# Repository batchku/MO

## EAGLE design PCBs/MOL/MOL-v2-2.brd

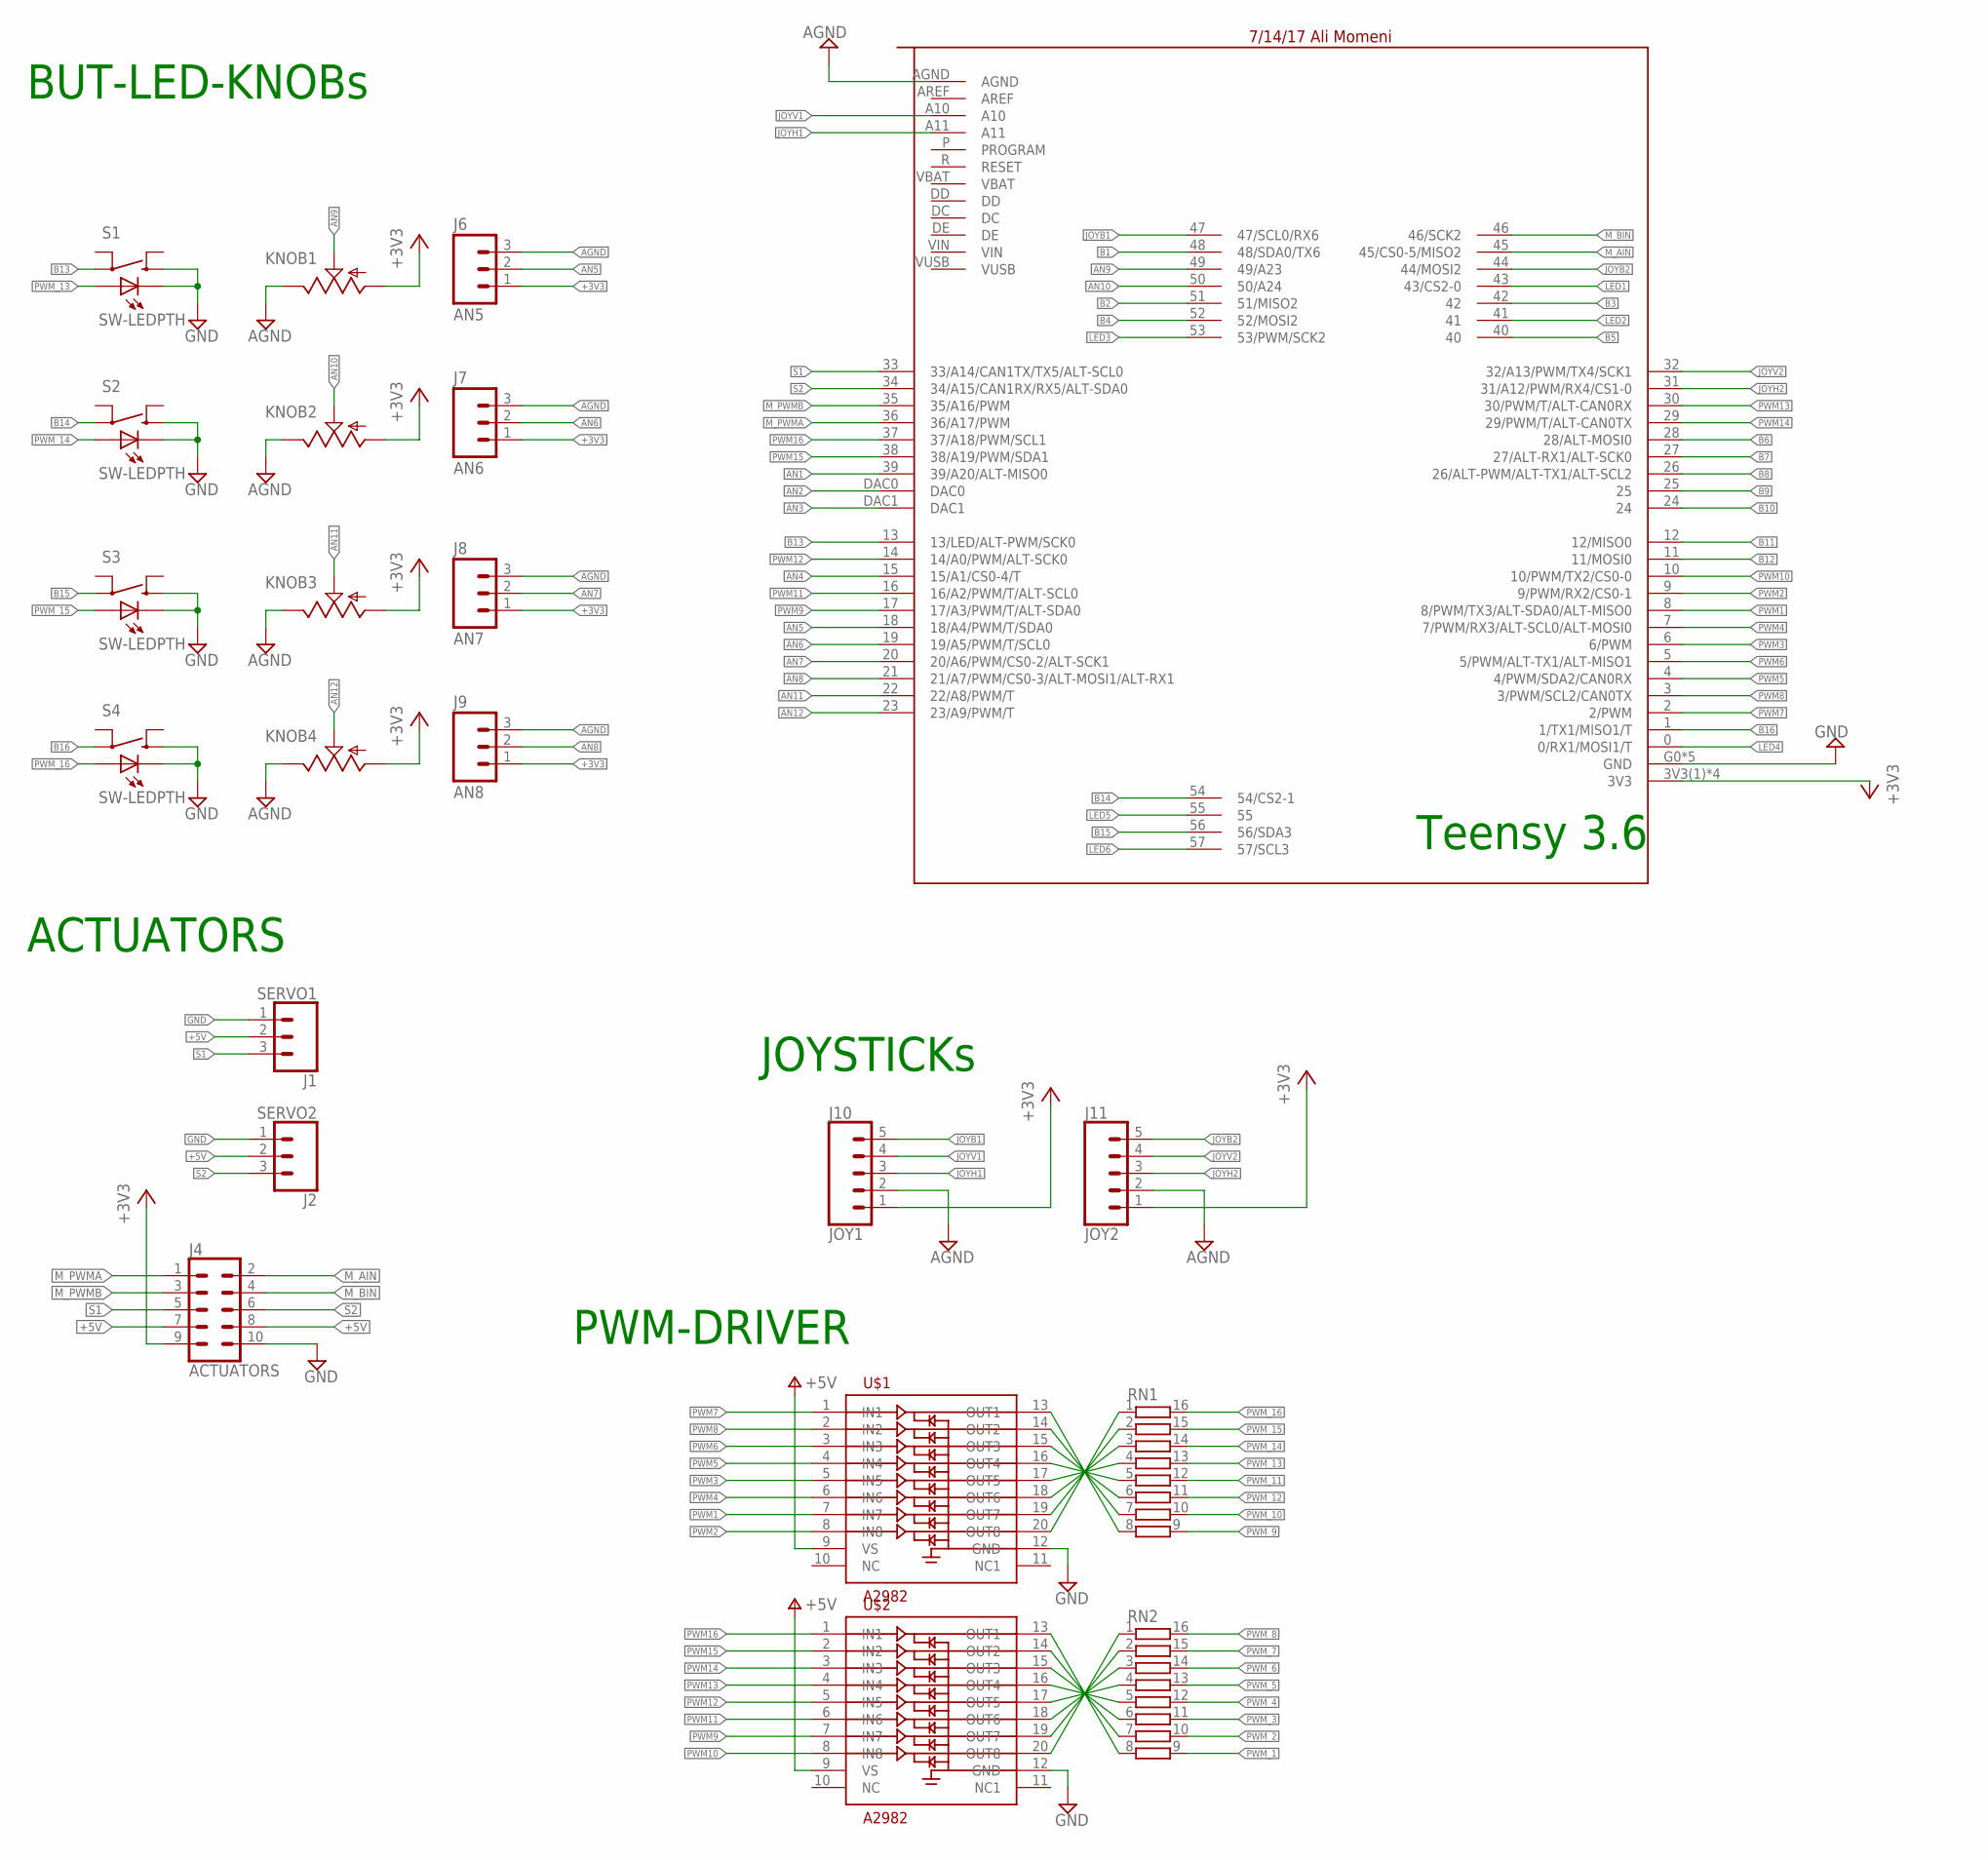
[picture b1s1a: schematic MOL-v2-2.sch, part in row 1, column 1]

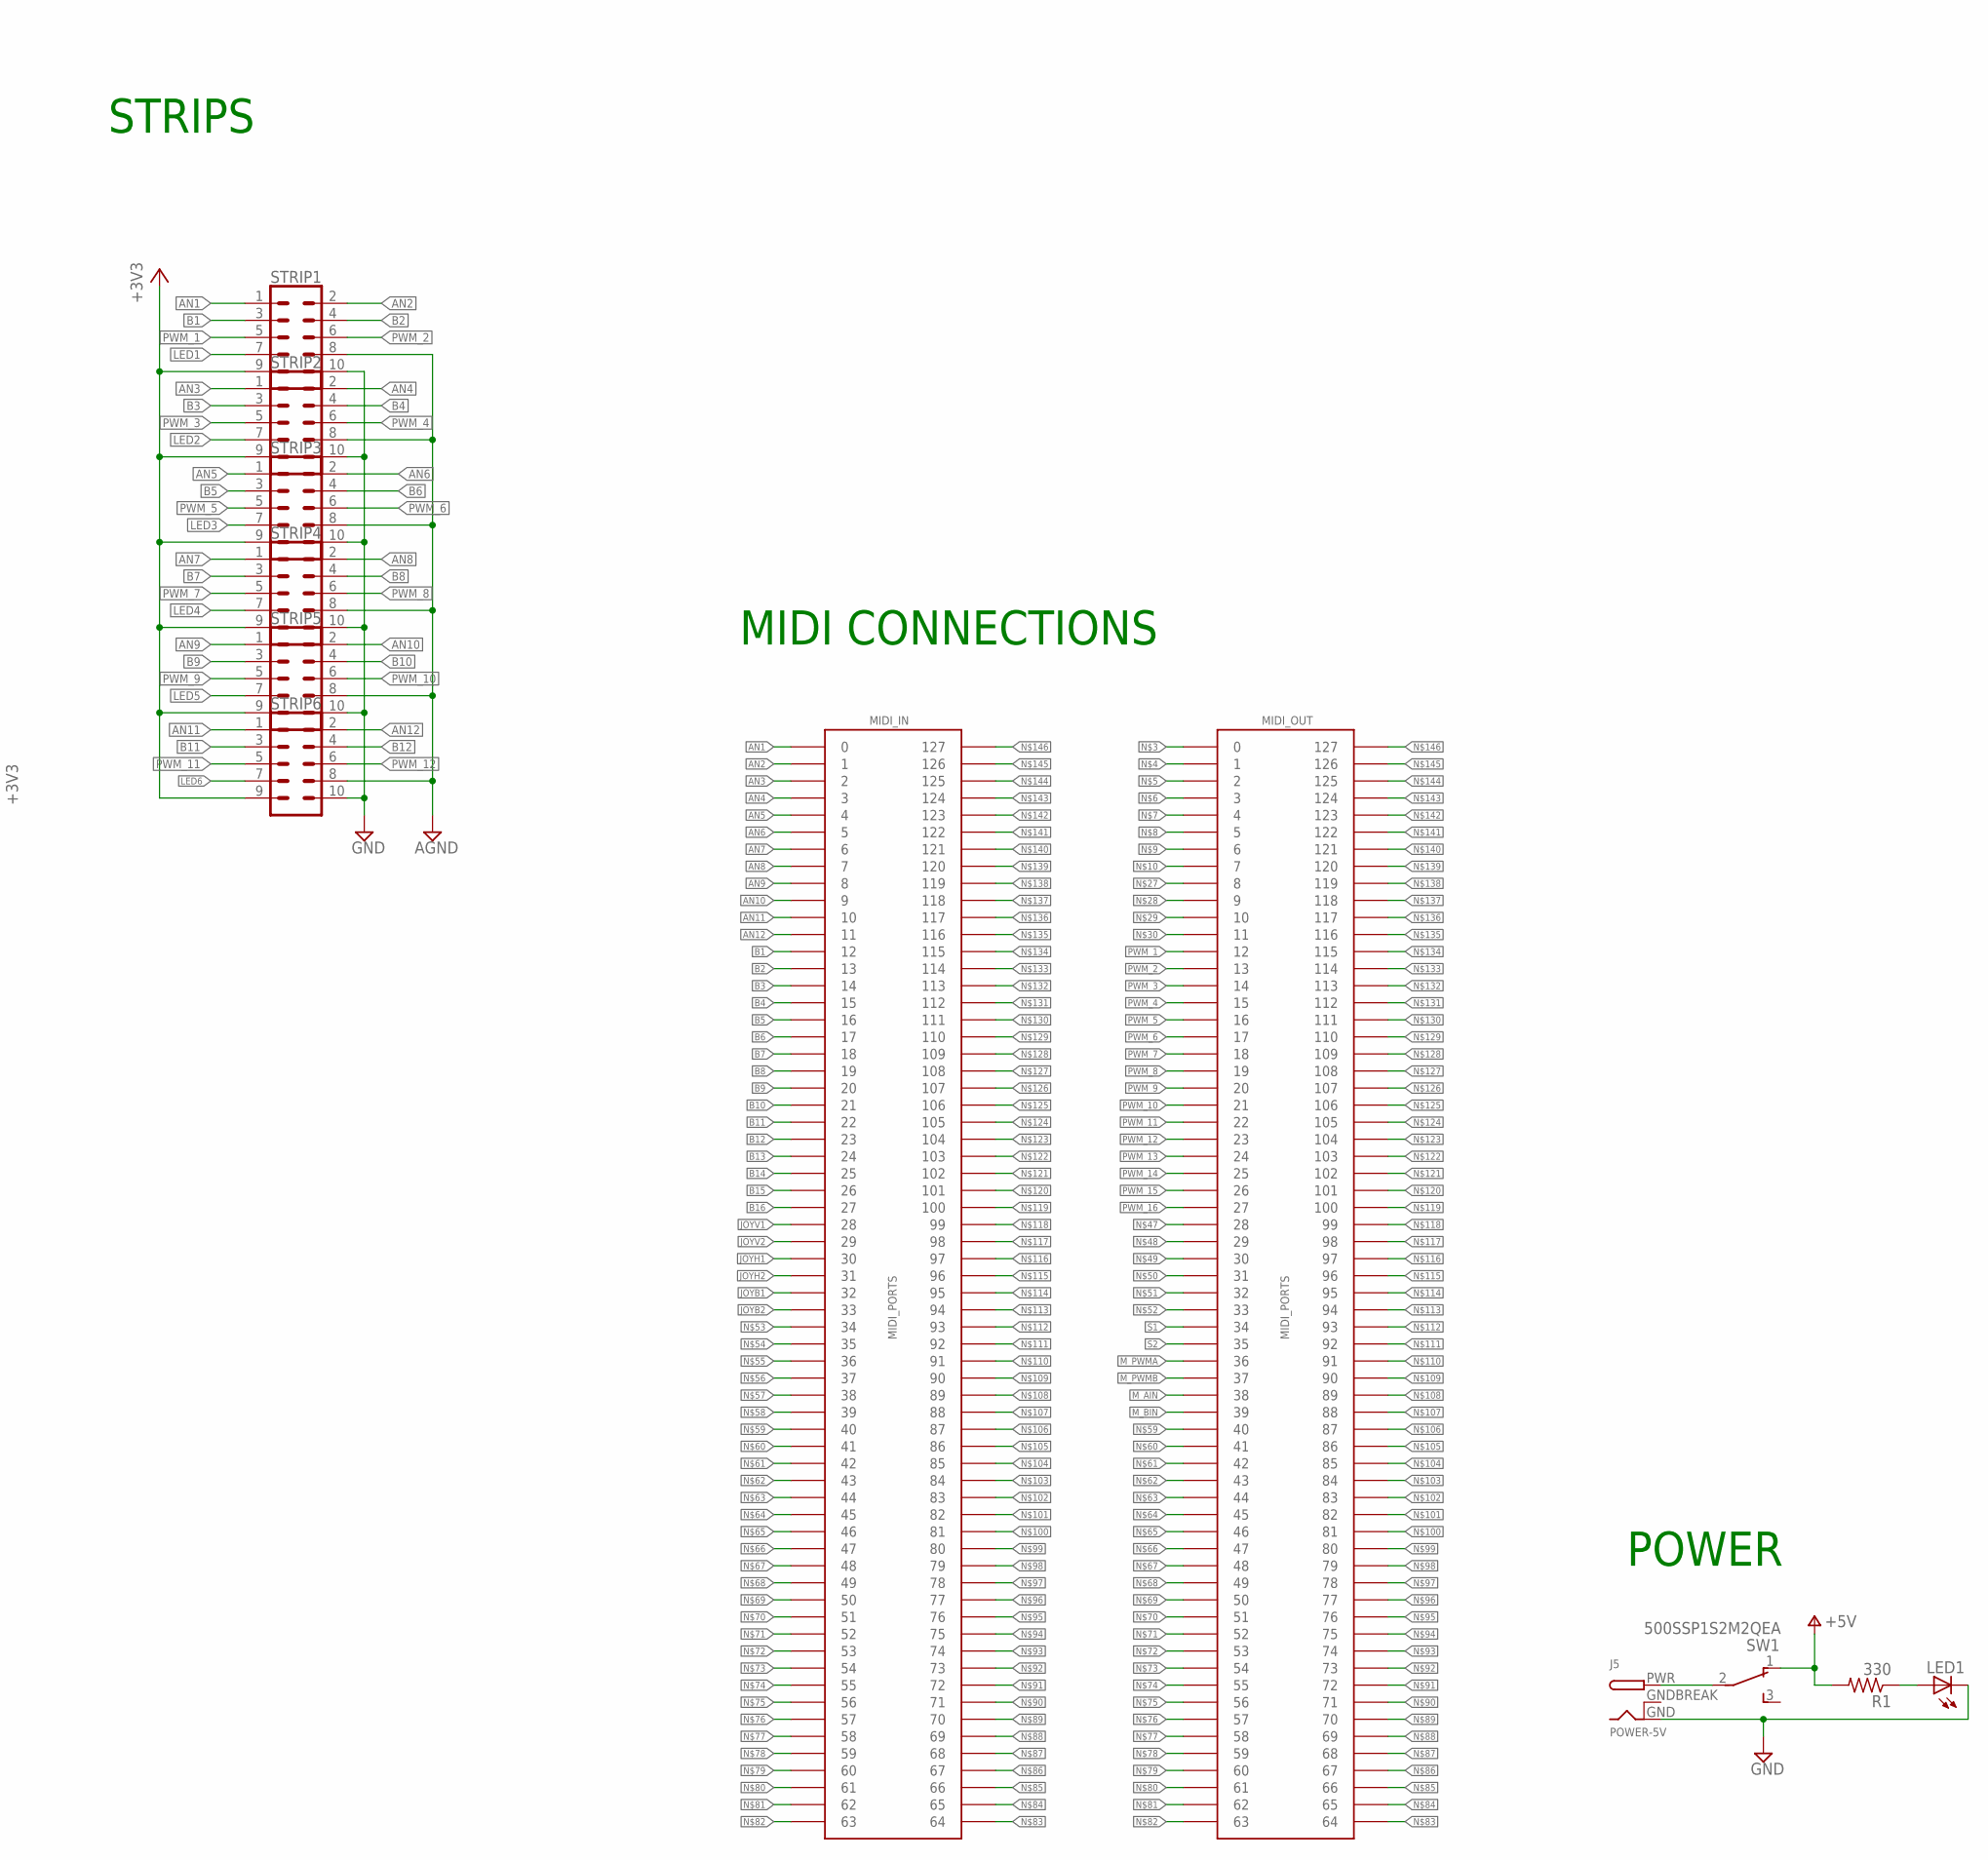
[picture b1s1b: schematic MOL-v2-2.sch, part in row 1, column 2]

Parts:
J1: SERVO1; 1X03_LOCK@1
J2: SERVO2; 1X03_LOCK@1
J4: ACTUATORS; 2X5-SHROUDED_LOCK
J5: POWER-5V; DCJACK_2MM_PTH
J6: AN5; 1X03_NO_SILK
J7: AN6; 1X03_NO_SILK
J8: AN7; 1X03_NO_SILK
J9: AN8; 1X03_NO_SILK
J10: JOY1; 1X05_LOCK
J11: JOY2; 1X05_LOCK
KNOB1, KNOB2, KNOB3, KNOB4: TRIM; TRIM-PCB-9MM
LED1: LED3MM
R1: 330; 0204/7
RN1, RN2: 2NBS16-8; SO16
S1, S2, S3, S4: SW-LEDPTH; SWITCH_TR2-MOMENTARY-LED
STRIP1, STRIP2, STRIP3, STRIP4, STRIP5, STRIP6: CONN_05X2SHD_LOCK; 2X5-SHROUDED_LOCK
SW1: 500SSP1S2M2QEA; SWITCH_SPDT_500SSP1S2M2QEA
TEENSY: TEENSY3_6-ALI_NO-USB-HOST; TEENSY3-6_NO-USB-HOST
U$1, U$2: A2982; SOIC20

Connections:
+3V3: J4.9, J6.1, J7.1, J8.1, J9.1, J10.1, J11.1, KNOB1.1 (A), KNOB2.1 (A), KNOB3.1 (A), KNOB4.1 (A), STRIP1.9, STRIP2.9, STRIP3.9, STRIP4.9, STRIP5.9, STRIP6.9, TEENSY.3V3(1) (3V3), TEENSY.3V3(2) (3V3), TEENSY.3V3(3) (3V3), TEENSY.3V3(4) (3V3)
+5V: J1.2, J2.2, J4.7, J4.8, R1.2, SW1.1
AGND: J6.3, J7.3, J8.3, J9.3, J10.2, J11.2, KNOB1.3 (E), KNOB2.3 (E), KNOB3.3 (E), KNOB4.3 (E), STRIP1.8, STRIP2.8, STRIP3.8, STRIP4.8, STRIP5.8, STRIP6.8, TEENSY.AGND
AN1: STRIP1.1, TEENSY.39 (39/A20/ALT-MISO0)
AN2: STRIP1.2, TEENSY.DAC0
AN3: STRIP2.1, TEENSY.DAC1
AN4: STRIP2.2, TEENSY.15 (15/A1/CS0-4/T)
AN5: J6.2, STRIP3.1, TEENSY.18 (18/A4/PWM/T/SDA0)
AN6: J7.2, STRIP3.2, TEENSY.19 (19/A5/PWM/T/SCL0)
AN7: J8.2, STRIP4.1, TEENSY.20 (20/A6/PWM/CS0-2/ALT-SCK1)
AN8: J9.2, STRIP4.2, TEENSY.21 (21/A7/PWM/CS0-3/ALT-MOSI1/ALT-RX1)
AN9: KNOB1.2 (S), STRIP5.1, TEENSY.49 (49/A23)
AN10: KNOB2.2 (S), STRIP5.2, TEENSY.50 (50/A24)
AN11: KNOB3.2 (S), STRIP6.1, TEENSY.22 (22/A8/PWM/T)
AN12: KNOB4.2 (S), STRIP6.2, TEENSY.23 (23/A9/PWM/T)
B1: STRIP1.3, TEENSY.48 (48/SDA0/TX6)
B2: STRIP1.4, TEENSY.51 (51/MISO2)
B3: STRIP2.3, TEENSY.42
B4: STRIP2.4, TEENSY.52 (52/MOSI2)
B5: STRIP3.3, TEENSY.40
B6: STRIP3.4, TEENSY.28 (28/ALT-MOSI0)
B7: STRIP4.3, TEENSY.27 (27/ALT-RX1/ALT-SCK0)
B8: STRIP4.4, TEENSY.26 (26/ALT-PWM/ALT-TX1/ALT-SCL2)
B9: STRIP5.3, TEENSY.25
B10: STRIP5.4, TEENSY.24
B11: STRIP6.3, TEENSY.12 (12/MISO0)
B12: STRIP6.4, TEENSY.11 (11/MOSI0)
B13: S1.3, TEENSY.13 (13/LED/ALT-PWM/SCK0)
B14: S2.3, TEENSY.54 (54/CS2-1)
B15: S3.3, TEENSY.56 (56/SDA3)
B16: S4.3, TEENSY.1 (1/TX1/MISO1/T)
GND: J1.1, J2.1, J4.10, J5.GND, LED1.K (C), S1.1, S1.C, S2.1, S2.C, S3.1, S3.C, S4.1, S4.C, STRIP1.10, STRIP2.10, STRIP3.10, STRIP4.10, STRIP5.10, STRIP6.10, TEENSY.G0 (GND), TEENSY.G1 (GND), TEENSY.G2 (GND), TEENSY.G3 (GND), TEENSY.G6 (GND), U$1.12 (GND), U$2.12 (GND)
GNDBREAK: J5.GNDBREAK
JOYB1: J10.5, TEENSY.47 (47/SCL0/RX6)
JOYB2: J11.5, TEENSY.44 (44/MOSI2)
JOYH1: J10.3, TEENSY.A11
JOYH2: J11.3, TEENSY.31 (31/A12/PWM/RX4/CS1-0)
JOYV1: J10.4, TEENSY.A10
JOYV2: J11.4, TEENSY.32 (32/A13/PWM/TX4/SCK1)
LED1: STRIP1.7, TEENSY.43 (43/CS2-0)
LED2: STRIP2.7, TEENSY.41
LED3: STRIP3.7, TEENSY.53 (53/PWM/SCK2)
LED4: STRIP4.7, TEENSY.0 (0/RX1/MOSI1/T)
LED5: STRIP5.7, TEENSY.55
LED6: STRIP6.7, TEENSY.57 (57/SCL3)
M_AIN: J4.2, TEENSY.45 (45/CS0-5/MISO2)
M_BIN: J4.4, TEENSY.46 (46/SCK2)
M_PWMA: J4.1, TEENSY.36 (36/A17/PWM)
M_PWMB: J4.3, TEENSY.35 (35/A16/PWM)
unnamed: J5.PWR, SW1.2
unnamed: LED1.A, R1.1
unnamed: RN1.8, U$1.13 (OUT1)
unnamed: RN1.7, U$1.14 (OUT2)
unnamed: RN1.6, U$1.15 (OUT3)
unnamed: RN1.5, U$1.16 (OUT4)
unnamed: RN1.4, U$1.17 (OUT5)
unnamed: RN1.3, U$1.18 (OUT6)
unnamed: RN1.2, U$1.19 (OUT7)
unnamed: RN1.1, U$1.20 (OUT8)
unnamed: RN2.1, U$2.20 (OUT8)
unnamed: RN2.2, U$2.19 (OUT7)
unnamed: RN2.3, U$2.18 (OUT6)
unnamed: RN2.4, U$2.17 (OUT5)
unnamed: RN2.5, U$2.16 (OUT4)
unnamed: RN2.6, U$2.15 (OUT3)
unnamed: RN2.7, U$2.14 (OUT2)
unnamed: RN2.8, U$2.13 (OUT1)
PWM1: TEENSY.8 (8/PWM/TX3/ALT-SDA0/ALT-MISO0), U$1.7 (IN7)
PWM2: TEENSY.9 (9/PWM/RX2/CS0-1), U$1.8 (IN8)
PWM3: TEENSY.6 (6/PWM), U$1.5 (IN5)
PWM4: TEENSY.7 (7/PWM/RX3/ALT-SCL0/ALT-MOSI0), U$1.6 (IN6)
PWM5: TEENSY.4 (4/PWM/SDA2/CAN0RX), U$1.4 (IN4)
PWM6: TEENSY.5 (5/PWM/ALT-TX1/ALT-MISO1), U$1.3 (IN3)
PWM7: TEENSY.2 (2/PWM), U$1.1 (IN1)
PWM8: TEENSY.3 (3/PWM/SCL2/CAN0TX), U$1.2 (IN2)
PWM9: TEENSY.17 (17/A3/PWM/T/ALT-SDA0), U$2.7 (IN7)
PWM10: TEENSY.10 (10/PWM/TX2/CS0-0), U$2.8 (IN8)
PWM11: TEENSY.16 (16/A2/PWM/T/ALT-SCL0), U$2.6 (IN6)
PWM12: TEENSY.14 (14/A0/PWM/ALT-SCK0), U$2.5 (IN5)
PWM13: TEENSY.30 (30/PWM/T/ALT-CAN0RX), U$2.4 (IN4)
PWM14: TEENSY.29 (29/PWM/T/ALT-CAN0TX), U$2.3 (IN3)
PWM15: TEENSY.38 (38/A19/PWM/SDA1), U$2.2 (IN2)
PWM16: TEENSY.37 (37/A18/PWM/SCL1), U$2.1 (IN1)
PWM_1: RN2.9, STRIP1.5
PWM_2: RN2.10, STRIP1.6
PWM_3: RN2.11, STRIP2.5
PWM_4: RN2.12, STRIP2.6
PWM_5: RN2.13, STRIP3.5
PWM_6: RN2.14, STRIP3.6
PWM_7: RN2.15, STRIP4.5
PWM_8: RN2.16, STRIP4.6
PWM_9: RN1.9, STRIP5.5
PWM_10: RN1.10, STRIP5.6
PWM_11: RN1.12, STRIP6.5
PWM_12: RN1.11, STRIP6.6
PWM_13: RN1.13, S1.A
PWM_14: RN1.14, S2.A
PWM_15: RN1.15, S3.A
PWM_16: RN1.16, S4.A
S1: J1.3, J4.5, TEENSY.33 (33/A14/CAN1TX/TX5/ALT-SCL0)
S2: J2.3, J4.6, TEENSY.34 (34/A15/CAN1RX/RX5/ALT-SDA0)
V+: U$1.9 (VS), U$2.9 (VS)

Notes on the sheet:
BUT-LED-KNOBs
JOYSTICKs
PWM-DRIVER
STRIPS
ACTUATORS
POWER
Teensy 3.6
MIDI CONNECTIONS

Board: 2 copper layers, 32 parts (13 on the bottom side), 101 nets, no tracks yet.

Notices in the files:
parts and their libraries:
SparkFun-Connectors: Licensing: Creative Commons ShareAlike 4.0 International - https://creativecommons.org/licenses/by-sa/4.0
